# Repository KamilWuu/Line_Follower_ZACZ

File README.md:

# Line_Follower_ZACZ
LineFollower robot created with my friend Oliwier W. Robot is made as a project for a mobile robots course in the sixth semester of the automation and robotics program at the Wrocaw University of Science and Technology.

test213

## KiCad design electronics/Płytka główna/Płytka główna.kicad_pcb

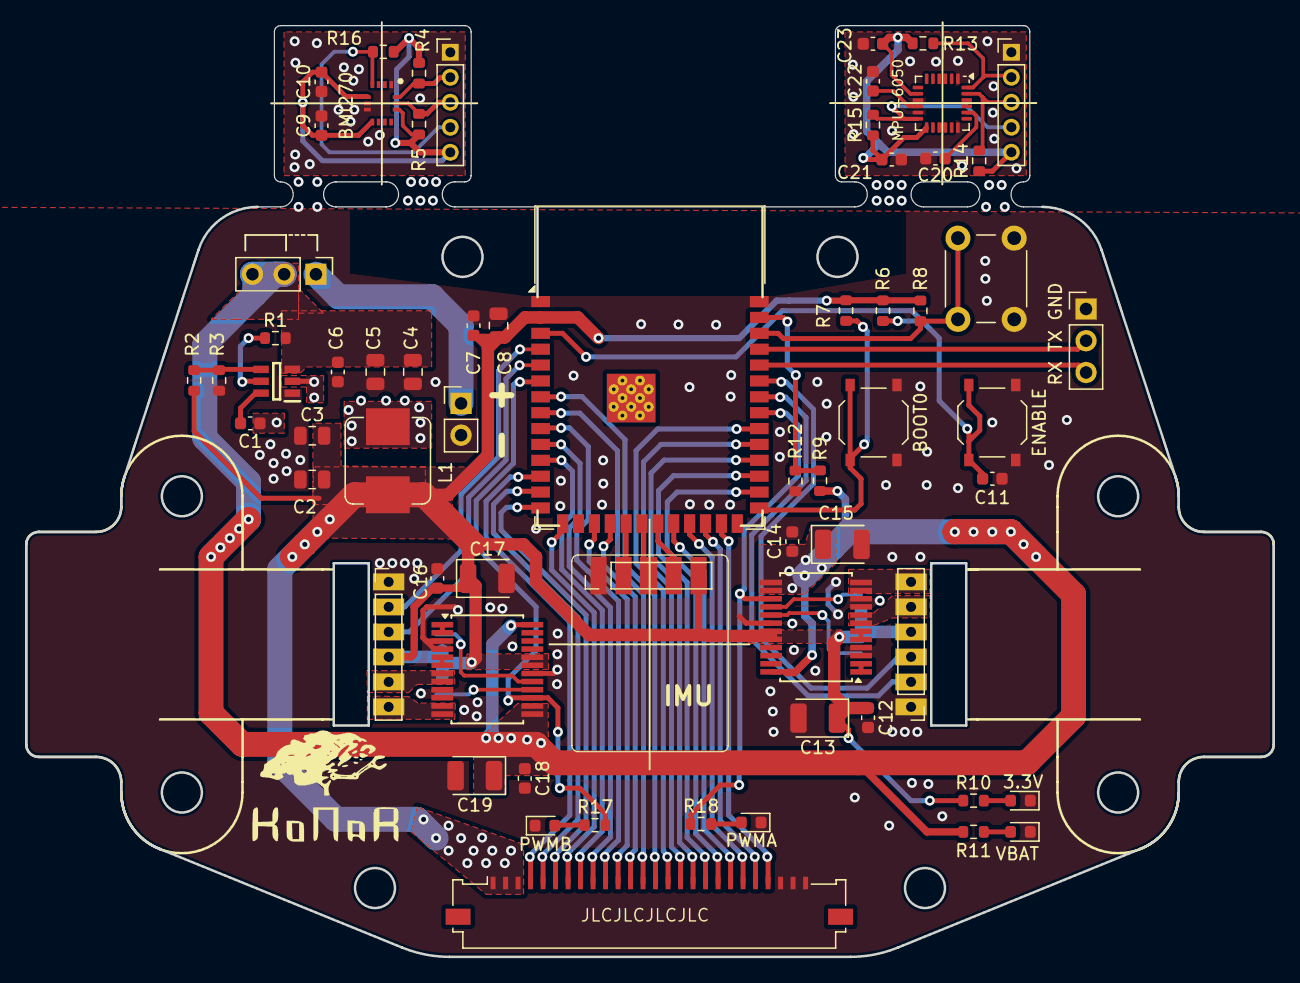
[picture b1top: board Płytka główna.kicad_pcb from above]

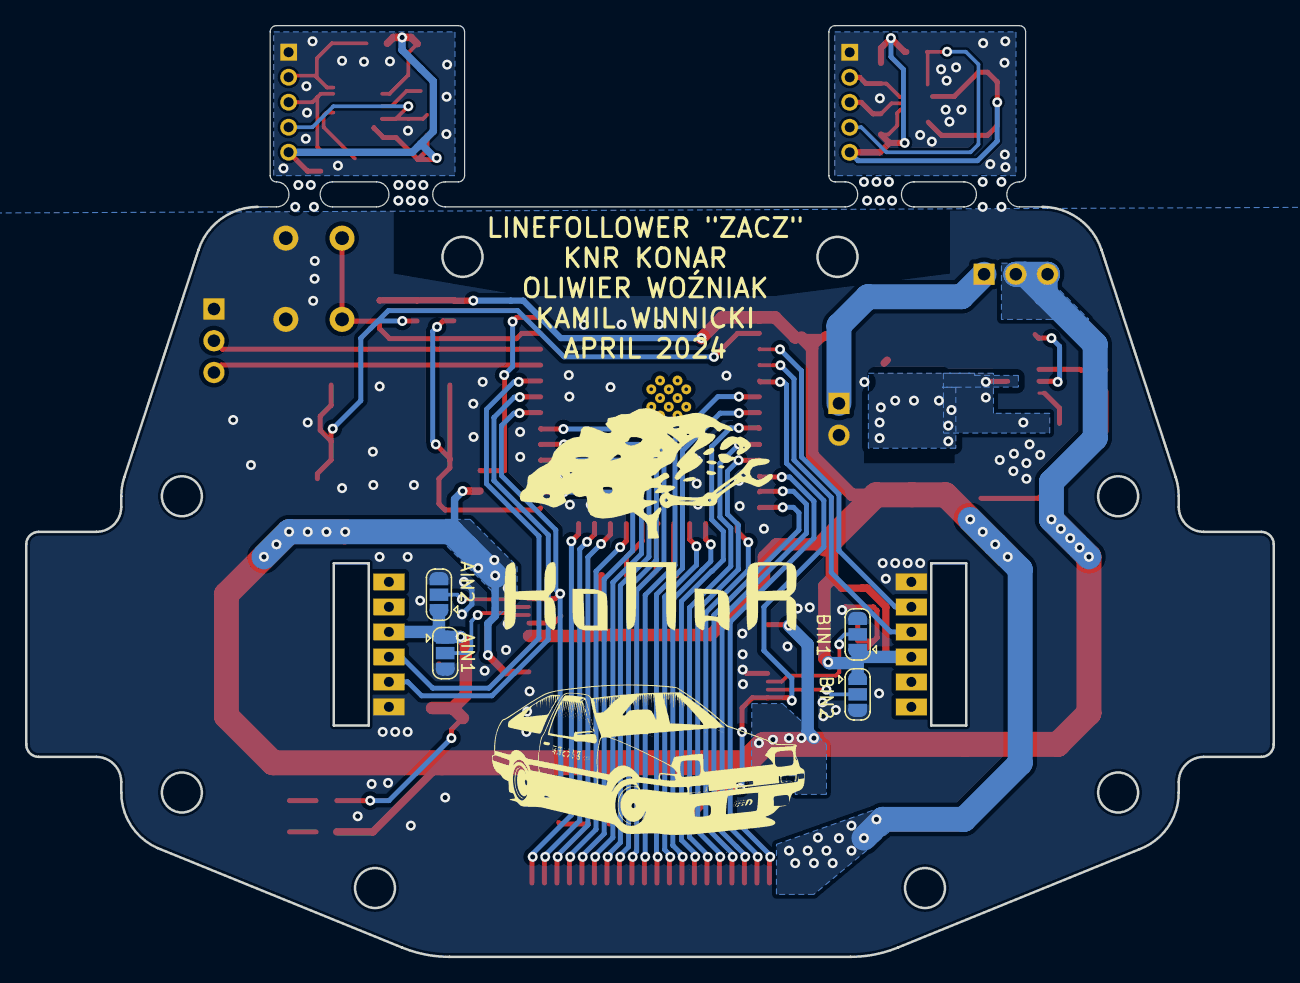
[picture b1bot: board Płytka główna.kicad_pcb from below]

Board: 2 copper layers, 99.8 x 74.5 mm, 68 parts (4 on the bottom side), 71 nets.

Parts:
3.3V: LED; LED_0603_1608Metric
AIN1, AIN2: SolderJumper_3_Open; SolderJumper-3_P1.3mm_Open_RoundedPad1.0x1.5mm
BIN1, BIN2: SolderJumper_3_Open; SolderJumper-3_P1.3mm_Open_RoundedPad1.0x1.5mm
BOOT0: SW_Push_Dual_x2; SW_Push_1P1T_XKB_TS-1187A
C1, C6, C7, C9, C10, C11, C12, C14, C16, C18, C21, C22: 0.1uF; C_0603_1608Metric
C2, C3, C8: 22uF; C_0805_2012Metric
C4, C5: 10uF; C_0805_2012Metric
C13, C17: >10uF/3.3V; CP_EIA-3528-21_Kemet-B
C15, C19: >10uF/8.4V; CP_EIA-3528-21_Kemet-B
C20: 2.2nF; C_0603_1608Metric
C23: 10nF; C_0603_1608Metric
ENABLE: SW_Push_Dual_x2; SW_Push_1P1T_XKB_TS-1187A
IC1: TPS563201DDCR; SOT95P280X110-6N
IC2: BMI270; QFN50P300X250X87-14N
J2: Conn_01x26_Socket; Molex_200528-0260_1x26-1MP_P1.00mm_Horizontal
J3, J4: Conn_01x06_Socket; PinHeader_1x06_P2.00mm_Vertical
J5: battery_connector; PinHeader_1x02_P2.54mm_Vertical
J6: Conn_01x03_Pin; PinHeader_1x03_P2.54mm_Vertical
J7: batt_switch; PinHeader_1x03_P2.54mm_Vertical
J8, J9, J10: Conn_01x05_Pin; PinHeader_1x05_P2.00mm_Vertical
L1: 2.2uH; L_Bourns_SRP7028A_7.3x6.6mm
MPU-6050: MPU-6050; InvenSense_QFN-24_4x4mm_P0.5mm
PWMA: LED; LED_0603_1608Metric
PWMB: LED; LED_0603_1608Metric
R1, R3: 10kR; R_0603_1608Metric
R2: 33.2kR; R_0603_1608Metric
R4, R5, R6, R7, R8, R13, R14, R15, R16: 10K; R_0603_1608Metric
R9, R12: ?; R_0603_1608Metric
R10: 220; R_0603_1608Metric
R11, R17, R18: 2K; R_0603_1608Metric
SW4: SW_Push_Dual_x2; SW_PUSH_6mm_H7.3mm
U1: ESP32-S3-WROOM-1-N8R8; ESP32-S3-WROOM-1
U2, U3: TB6612FNG; SSOP-24_5.3x8.2mm_P0.65mm
VBAT: LED; LED_0603_1608Metric

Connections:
+3.3V: AIN1.1 (A), AIN2.1 (A), BIN1.1 (A), BIN2.1 (A), C2.2, C3.2, C7.2, C8.2, C12.1, C13.1, C16.1, C17.1, J2.1, J2.2, J2.3, J3.4, J4.4, J9.5, L1.1, R2.2, R6.1, R7.1, R8.1, R10.1, U1.2 (3V3), U2.19 (STBY), U2.20 (VCC), U3.19 (STBY), U3.20 (VCC)
+3.3V_BMI: C9.1, C10.2, IC2.5 (VDDIO), IC2.8 (VDD), IC2.12 (CSB), J10.5, R4.1, R5.1, R16.1
+3.3V_MPU: C21.2, C23.2, J8.5, MPU-6050.8 (VLOGIC), MPU-6050.13 (VDD), R13.1, R14.1, R15.1
+BATT: C4.1, C5.1, C6.1, C14.1, C15.1, C18.1, C19.1, IC1.3 (VIN), J7.2, J7.3, R1.2, R9.1, R11.1, U2.13 (VM2), U2.14 (VM3), U2.24 (VM1), U3.13 (VM2), U3.14 (VM3), U3.24 (VM1)
AIN1: AIN1.2 (C), U2.17 (BIN1)
AIN2: AIN2.2 (C), U2.16 (BIN2)
AO1: J3.6, U2.11 (BO1), U2.12 (BO1)
AO2: J3.5, U2.7 (BO2), U2.8 (BO2)
BIN1: BIN1.2 (C), U3.17 (BIN1)
BIN2: BIN2.2 (C), U3.16 (BIN2)
BO1: J4.6, U3.11 (BO1), U3.12 (BO1)
BO2: J4.5, U3.7 (BO2), U3.8 (BO2)
BUTTON: R8.2, SW4.2 (D), U1.38 (IO2)
EN: C11.2, ENABLE.2 (D), R6.2, U1.3 (EN)
ENC_A1: J3.3, U1.35 (IO42)
ENC_A2: J3.2, U1.34 (IO41)
ENC_B1: J4.3, U1.5 (IO5)
ENC_B2: J4.2, U1.4 (IO4)
GND: 3.3V.1 (K), AIN1.3 (B), AIN2.3 (B), BIN1.3 (B), BIN2.3 (B), BOOT0.1 (C), C2.1, C3.1, C4.2, C5.2, C6.2, C7.1, C8.1, C11.1, C12.2, C13.2, C14.2, C15.2, C16.2, C17.2, C18.2, C19.2, ENABLE.1 (C), IC1.1 (GND), J2.24, J2.25, J2.26, J3.1, J4.1, J5.2, J6.1, J9.1, PWMA.1 (K), PWMB.1 (K), R3.1, R12.2, SW4.1 (C), U1.1 (GND), U1.40 (GND), U2.3 (PGND1), U2.4 (PGND1), U2.9 (PGND2), U2.10 (PGND2), U2.18 (GND), U3.3 (PGND1), U3.4 (PGND1), U3.9 (PGND2), U3.10 (PGND2), U3.18 (GND), VBAT.1 (K)
GND_BMI: C9.2, C10.1, IC2.1 (SDO), IC2.6 (GNDIO), IC2.7 (GND), J10.1
GND_MPU: C20.1, C21.1, C22.2, C23.1, J8.1, MPU-6050.1 (CLKIN), MPU-6050.9 (AD0), MPU-6050.11 (FSYNC), MPU-6050.18 (GND)
IMU_INT: J9.4, U1.21 (IO13)
INT_BMI: IC2.4 (INT1), J10.4, R16.2
INT_MPU: J8.4, MPU-6050.12 (INT), R15.2
IO0: BOOT0.2 (D), R7.2, U1.27 (IO0)
IR_SIG_01: J2.4, U1.12 (IO8)
IR_SIG_02: J2.5, U1.13 (IO19)
IR_SIG_03: J2.6, U1.14 (IO20)
IR_SIG_04: J2.7, U1.15 (IO3)
IR_SIG_05: J2.8, U1.11 (IO18)
IR_SIG_06: J2.9, U1.10 (IO17)
IR_SIG_07: J2.10, U1.9 (IO16)
IR_SIG_08: J2.11, U1.17 (IO9)
IR_SIG_09: J2.12, U1.18 (IO10)
IR_SIG_10: J2.13, U1.8 (IO15)
IR_SIG_11: J2.14, U1.7 (IO7)
IR_SIG_12: J2.15, U1.32 (IO39)
IR_SIG_13: J2.16, U1.31 (IO38)
IR_SIG_14: J2.17, U1.30 (IO37)
IR_SIG_15: J2.18, U1.29 (IO36)
IR_SIG_16: J2.19, U1.28 (IO35)
IR_SIG_17: J2.20, U1.22 (IO14)
IR_SIG_18: J2.21, U1.23 (IO21)
IR_SIG_19: J2.22, U1.24 (IO47)
IR_SIG_20: J2.23, U1.25 (IO48)
unnamed: 3.3V.2 (A), R10.2
unnamed: IC1.5 (EN), R1.1
unnamed: C1.2, IC1.6 (VBST)
unnamed: IC1.4 (VFB), R2.1, R3.2
unnamed: J5.1, J7.1
unnamed: C20.2, MPU-6050.20 (CPOUT)
unnamed: C22.1, MPU-6050.10 (REGOUT)
unnamed: PWMA.2 (A), R18.2
unnamed: PWMB.2 (A), R17.2
unnamed: U2.1 (AO1), U2.2 (AO1)
unnamed: U2.5 (AO2), U2.6 (AO2)
unnamed: U3.1 (AO1), U3.2 (AO1)
unnamed: U3.5 (AO2), U3.6 (AO2)
unnamed: R11.2, VBAT.2 (A)
PWMA: R18.1, U1.33 (IO40), U2.15 (PWMB)
PWMB: R17.1, U1.6 (IO6), U3.15 (PWMB)
RX: J6.3, U1.36 (RXD0)
SCL_I2C: J9.3, U1.20 (IO12)
SCL_I2C_BMI: IC2.13 (SCX), J10.3, R5.2
SCL_I2C_MPU: J8.3, MPU-6050.23 (SCL), R14.2
SDA_I2C: J9.2, U1.19 (IO11)
SDA_I2C_BMI: IC2.14 (SDX), J10.2, R4.2
SDA_I2C_MPU: J8.2, MPU-6050.24 (SDA), R13.2
SW: C1.1, IC1.2 (SW), L1.2
TX: J6.2, U1.37 (TXD0)
V_BAT: R9.2, R12.1, U1.39 (IO1)

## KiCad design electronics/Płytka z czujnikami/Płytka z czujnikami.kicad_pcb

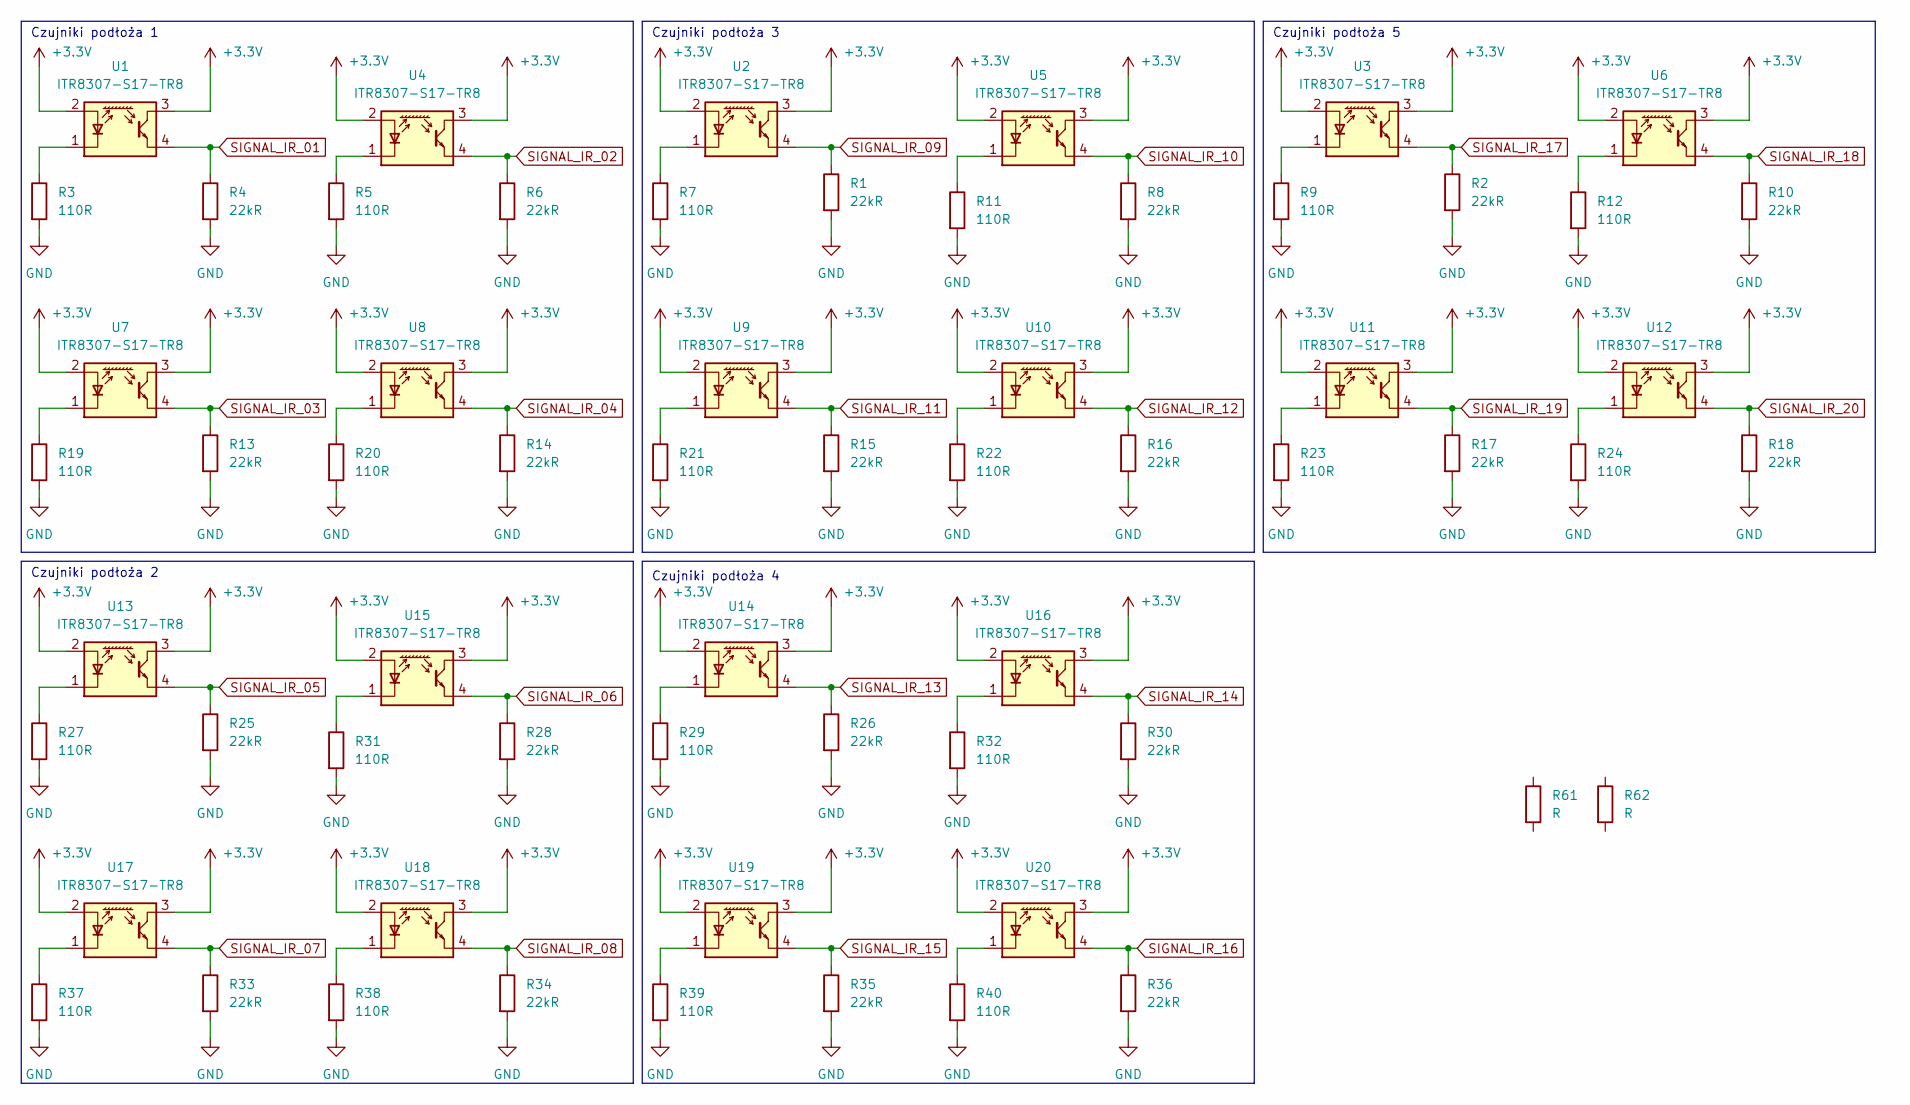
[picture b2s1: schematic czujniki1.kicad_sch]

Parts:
R1, R2, R4, R6, R8, R10, R13, R14, R15, R16, R17, R18, R25, R26, R28, R30, R33, R34, R35, R36: 22kR; R_0402_1005Metric_Pad0.72x0.64mm_HandSolder
R3, R5, R7, R9, R11, R12, R19, R20, R21, R22, R23, R24, R27, R29, R31, R32, R37, R38, R39, R40: 110R; R_0402_1005Metric_Pad0.72x0.64mm_HandSolder
R61, R62: R; R_Axial_DIN0207_L6.3mm_D2.5mm_P10.16mm_Horizontal
U1, U2, U3, U4, U5, U6, U7, U8, U9, U10, U11, U12, U13, U14, U15, U16, U17, U18, U19, U20: ITR8307-S17-TR8; Everlight_ITR1201SR10AR

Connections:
+3.3V: U1.2 (A), U1.3, U2.2 (A), U2.3, U3.2 (A), U3.3, U4.2 (A), U4.3, U5.2 (A), U5.3, U6.2 (A), U6.3, U7.2 (A), U7.3, U8.2 (A), U8.3, U9.2 (A), U9.3, U10.2 (A), U10.3, U11.2 (A), U11.3, U12.2 (A), U12.3, U13.2 (A), U13.3, U14.2 (A), U14.3, U15.2 (A), U15.3, U16.2 (A), U16.3, U17.2 (A), U17.3, U18.2 (A), U18.3, U19.2 (A), U19.3, U20.2 (A), U20.3; also elsewhere on the board
GND: R1.2, R2.2, R3.2, R4.2, R5.2, R6.2, R7.2, R8.2, R9.2, R10.2, R11.2, R12.2, R13.2, R14.2, R15.2, R16.2, R17.2, R18.2, R19.2, R20.2, R21.2, R22.2, R23.2, R24.2, R25.2, R26.2, R27.2, R28.2, R29.2, R30.2, R31.2, R32.2, R33.2, R34.2, R35.2, R36.2, R37.2, R38.2, R39.2, R40.2; also elsewhere on the board
unnamed: R3.1, U1.1 (K)
unnamed: R7.1, U2.1 (K)
unnamed: R9.1, U3.1 (K)
unnamed: R5.1, U4.1 (K)
unnamed: R11.1, U5.1 (K)
unnamed: R12.1, U6.1 (K)
unnamed: R19.1, U7.1 (K)
unnamed: R20.1, U8.1 (K)
unnamed: R21.1, U9.1 (K)
unnamed: R22.1, U10.1 (K)
unnamed: R23.1, U11.1 (K)
unnamed: R24.1, U12.1 (K)
unnamed: R27.1, U13.1 (K)
unnamed: R29.1, U14.1 (K)
unnamed: R31.1, U15.1 (K)
unnamed: R32.1, U16.1 (K)
unnamed: R37.1, U17.1 (K)
unnamed: R38.1, U18.1 (K)
unnamed: R39.1, U19.1 (K)
unnamed: R40.1, U20.1 (K)
SIGNAL_IR_01: R4.1, U1.4; also elsewhere on the board
SIGNAL_IR_02: R6.1, U4.4; also elsewhere on the board
SIGNAL_IR_03: R13.1, U7.4; also elsewhere on the board
SIGNAL_IR_04: R14.1, U8.4; also elsewhere on the board
SIGNAL_IR_05: R25.1, U13.4; also elsewhere on the board
SIGNAL_IR_06: R28.1, U15.4; also elsewhere on the board
SIGNAL_IR_07: R33.1, U17.4; also elsewhere on the board
SIGNAL_IR_08: R34.1, U18.4; also elsewhere on the board
SIGNAL_IR_09: R1.1, U2.4; also elsewhere on the board
SIGNAL_IR_10: R8.1, U5.4; also elsewhere on the board
SIGNAL_IR_11: R15.1, U9.4; also elsewhere on the board
SIGNAL_IR_12: R16.1, U10.4; also elsewhere on the board
SIGNAL_IR_13: R26.1, U14.4; also elsewhere on the board
SIGNAL_IR_14: R30.1, U16.4; also elsewhere on the board
SIGNAL_IR_15: R35.1, U19.4; also elsewhere on the board
SIGNAL_IR_16: R36.1, U20.4; also elsewhere on the board
SIGNAL_IR_17: R2.1, U3.4; also elsewhere on the board
SIGNAL_IR_18: R10.1, U6.4; also elsewhere on the board
SIGNAL_IR_19: R17.1, U11.4; also elsewhere on the board
SIGNAL_IR_20: R18.1, U12.4; also elsewhere on the board

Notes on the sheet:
Czujniki podłoża 2
Czujniki podłoża 4
Czujniki podłoża 5
Czujniki podłoża 1
Czujniki podłoża 3

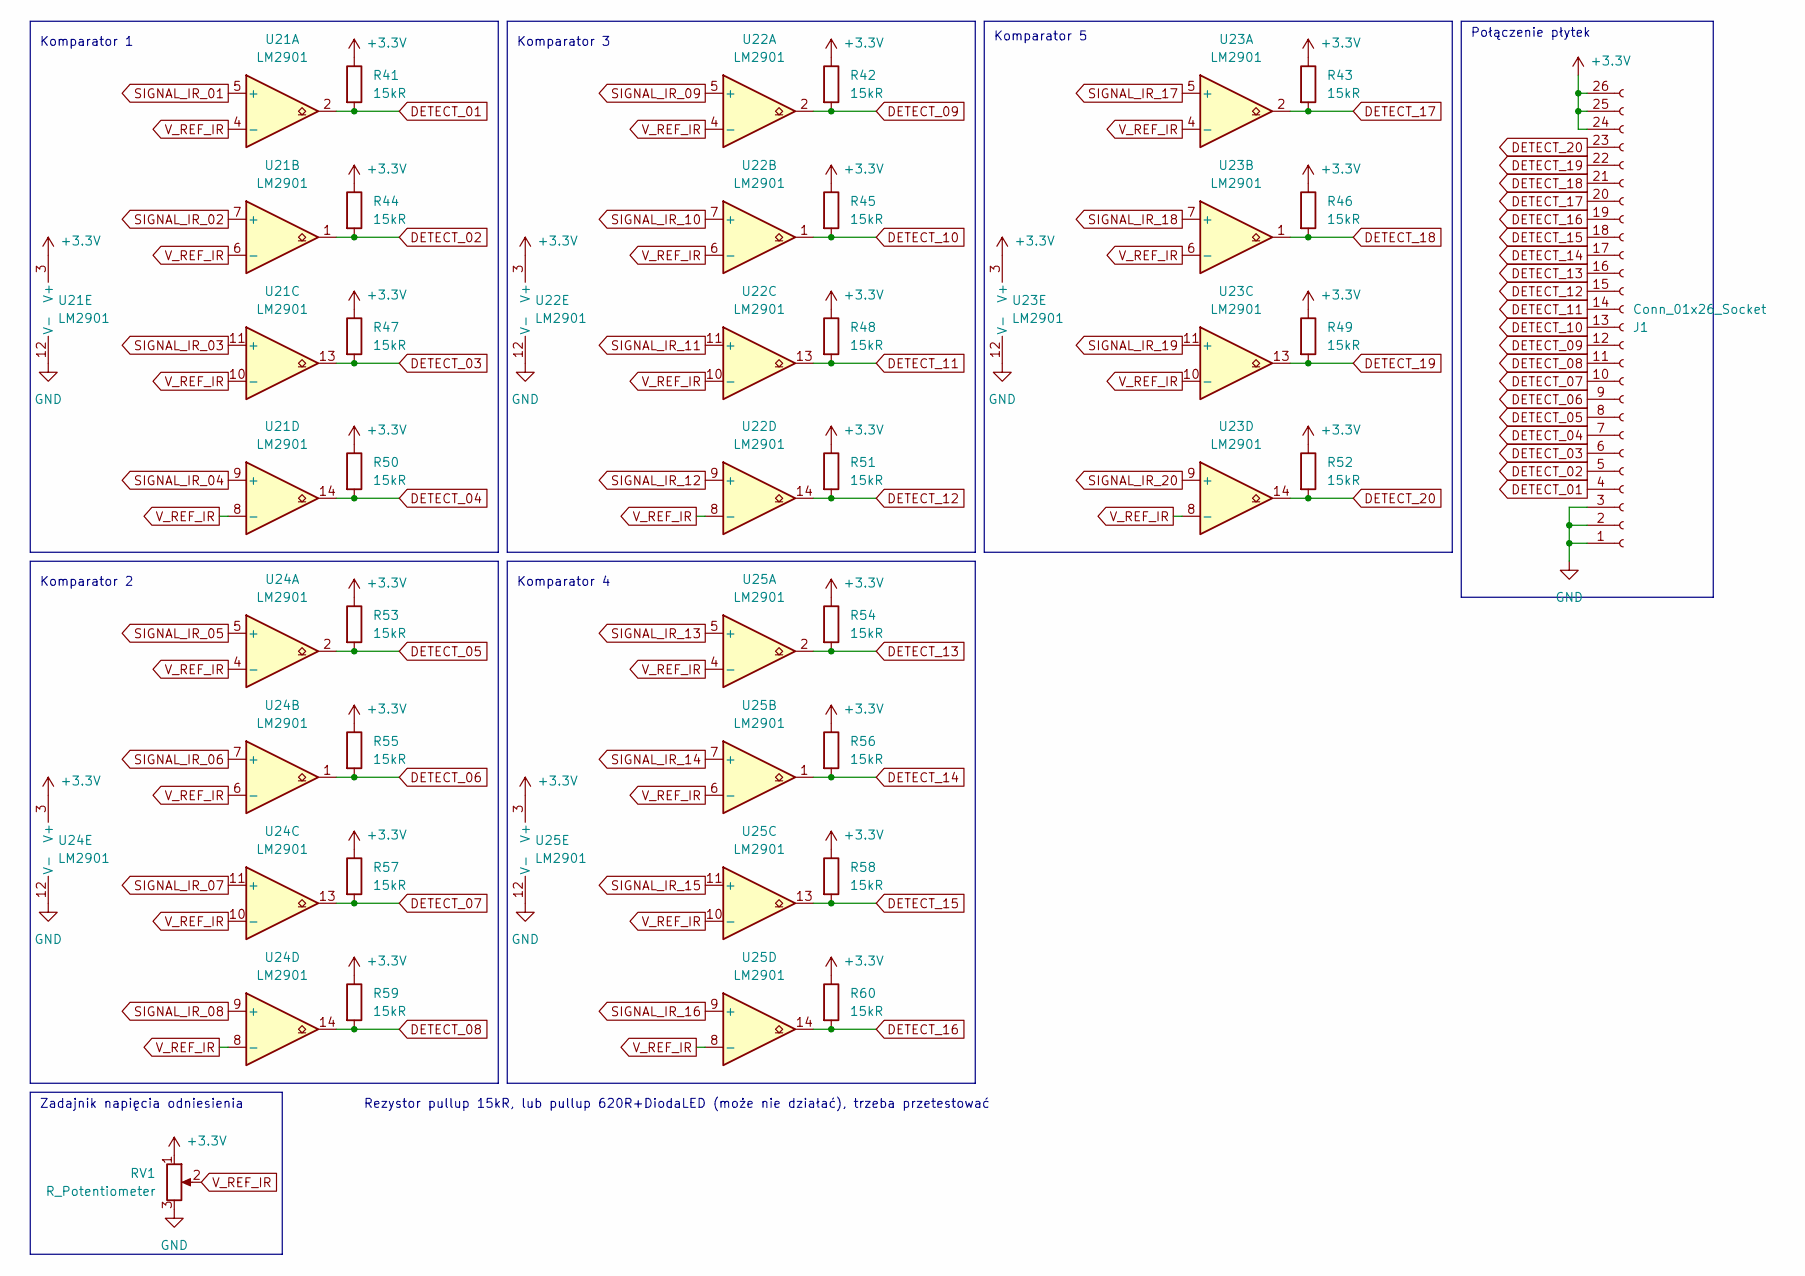
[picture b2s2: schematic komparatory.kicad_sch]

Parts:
J1: Conn_01x26_Socket; Molex_200528-0260_1x26-1MP_P1.00mm_Horizontal
R41, R42, R43, R44, R45, R46, R47, R48, R49, R50, R51, R52, R53, R54, R55, R56, R57, R58, R59, R60: 15kR; R_0402_1005Metric_Pad0.72x0.64mm_HandSolder
RV1: R_Potentiometer; Potentiometer_Vishay_TS53YJ_Vertical
U21, U22, U23, U24, U25: LM2901; SO-14_5.3x10.2mm_P1.27mm

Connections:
+3.3V: J1.24, J1.25, J1.26, R41.1, R42.1, R43.1, R44.1, R45.1, R46.1, R47.1, R48.1, R49.1, R50.1, R51.1, R52.1, R53.1, R54.1, R55.1, R56.1, R57.1, R58.1, R59.1, R60.1, RV1.1, U21.3 (V+), U22.3 (V+), U23.3 (V+), U24.3 (V+), U25.3 (V+); also elsewhere on the board
DETECT_01: J1.4, R41.2, U21.2
DETECT_02: J1.5, R44.2, U21.1
DETECT_03: J1.6, R47.2, U21.13
DETECT_04: J1.7, R50.2, U21.14
DETECT_05: J1.8, R53.2, U24.2
DETECT_06: J1.9, R55.2, U24.1
DETECT_07: J1.10, R57.2, U24.13
DETECT_08: J1.11, R59.2, U24.14
DETECT_09: J1.12, R42.2, U22.2
DETECT_10: J1.13, R45.2, U22.1
DETECT_11: J1.14, R48.2, U22.13
DETECT_12: J1.15, R51.2, U22.14
DETECT_13: J1.16, R54.2, U25.2
DETECT_14: J1.17, R56.2, U25.1
DETECT_15: J1.18, R58.2, U25.13
DETECT_16: J1.19, R60.2, U25.14
DETECT_17: J1.20, R43.2, U23.2
DETECT_18: J1.21, R46.2, U23.1
DETECT_19: J1.22, R49.2, U23.13
DETECT_20: J1.23, R52.2, U23.14
GND: J1.1, J1.2, J1.3, RV1.3, U21.12 (V-), U22.12 (V-), U23.12 (V-), U24.12 (V-), U25.12 (V-); also elsewhere on the board
SIGNAL_IR_01: U21.5 (+); also elsewhere on the board
SIGNAL_IR_02: U21.7 (+); also elsewhere on the board
SIGNAL_IR_03: U21.11 (+); also elsewhere on the board
SIGNAL_IR_04: U21.9 (+); also elsewhere on the board
SIGNAL_IR_05: U24.5 (+); also elsewhere on the board
SIGNAL_IR_06: U24.7 (+); also elsewhere on the board
SIGNAL_IR_07: U24.11 (+); also elsewhere on the board
SIGNAL_IR_08: U24.9 (+); also elsewhere on the board
SIGNAL_IR_09: U22.5 (+); also elsewhere on the board
SIGNAL_IR_10: U22.7 (+); also elsewhere on the board
SIGNAL_IR_11: U22.11 (+); also elsewhere on the board
SIGNAL_IR_12: U22.9 (+); also elsewhere on the board
SIGNAL_IR_13: U25.5 (+); also elsewhere on the board
SIGNAL_IR_14: U25.7 (+); also elsewhere on the board
SIGNAL_IR_15: U25.11 (+); also elsewhere on the board
SIGNAL_IR_16: U25.9 (+); also elsewhere on the board
SIGNAL_IR_17: U23.5 (+); also elsewhere on the board
SIGNAL_IR_18: U23.7 (+); also elsewhere on the board
SIGNAL_IR_19: U23.11 (+); also elsewhere on the board
SIGNAL_IR_20: U23.9 (+); also elsewhere on the board
V_REF_IR: RV1.2, U21.4 (-), U21.6 (-), U21.8 (-), U21.10 (-), U22.4 (-), U22.6 (-), U22.8 (-), U22.10 (-), U23.4 (-), U23.6 (-), U23.8 (-), U23.10 (-), U24.4 (-), U24.6 (-), U24.8 (-), U24.10 (-), U25.4 (-), U25.6 (-), U25.8 (-), U25.10 (-)

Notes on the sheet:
Komparator 1
Połączenie płytek
Komparator 4
Komparator 3
Zadajnik napięcia odniesienia
Komparator 2
Komparator 5
Rezystor pullup 15kR, lub pullup 620R+DiodaLED (może nie działać), trzeba przetestować

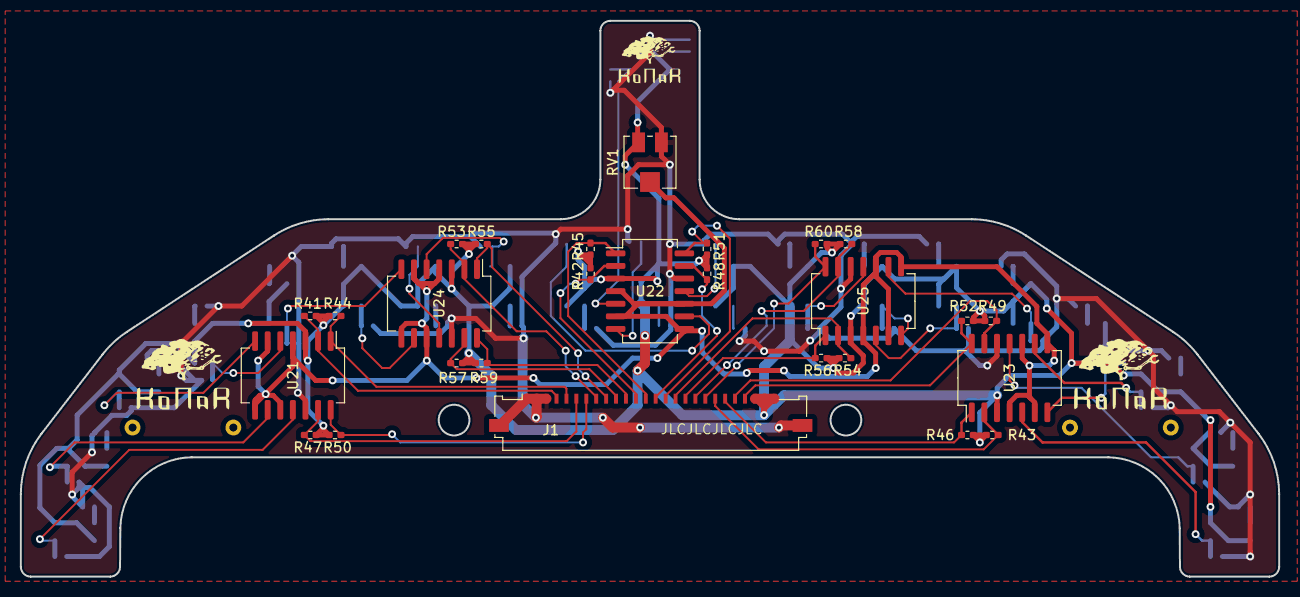
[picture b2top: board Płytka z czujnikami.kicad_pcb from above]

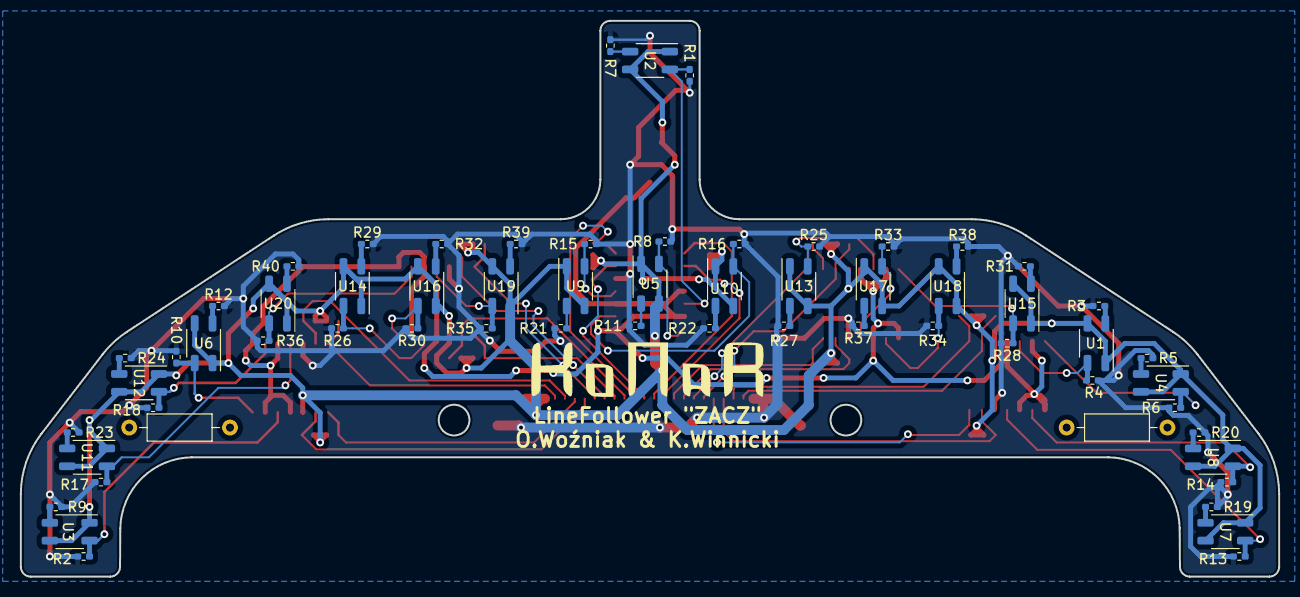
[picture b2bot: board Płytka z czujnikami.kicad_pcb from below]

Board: 2 copper layers, 126.8 x 56.0 mm, 89 parts (62 on the bottom side), 63 nets.

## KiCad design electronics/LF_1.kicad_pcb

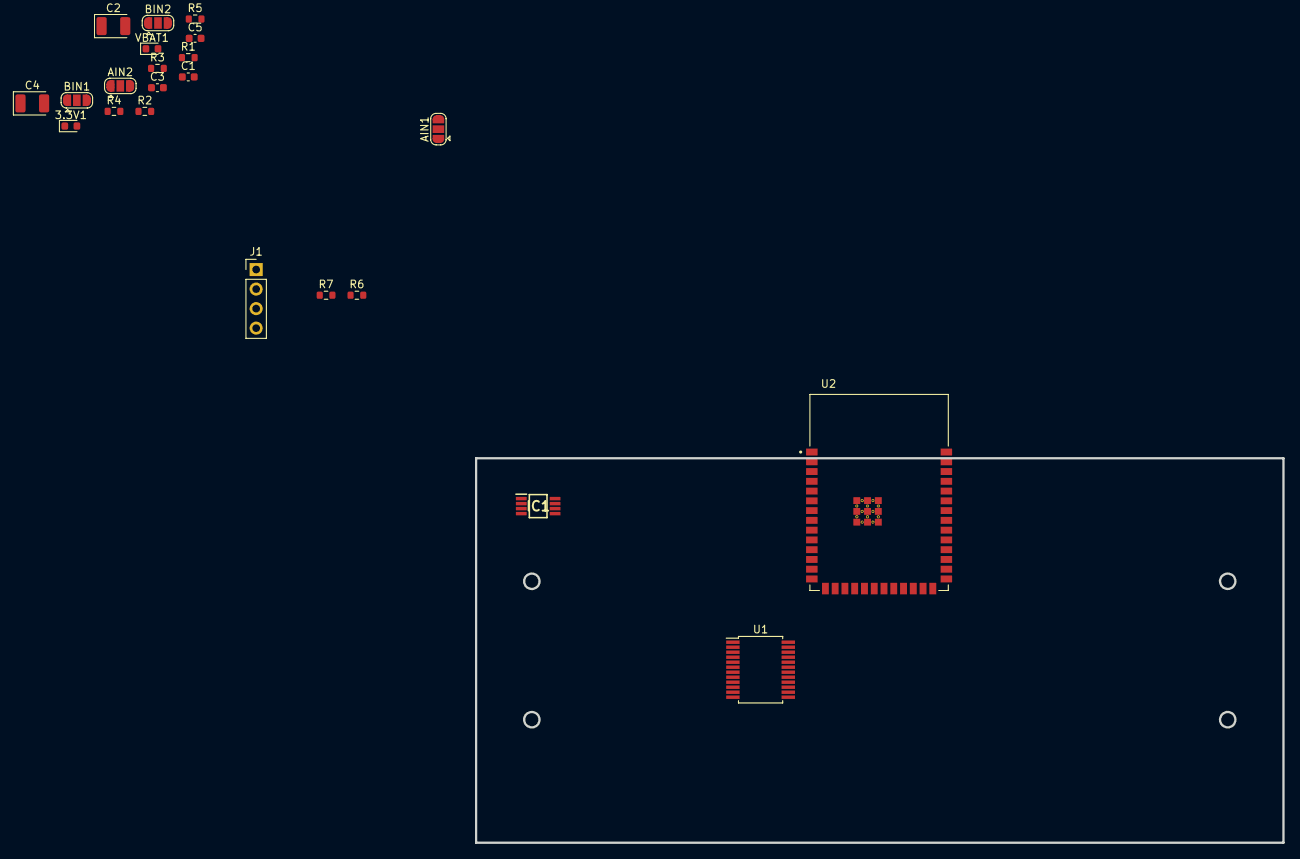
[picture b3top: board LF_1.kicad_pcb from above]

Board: 2 copper layers, 105.0 x 50.0 mm, 22 parts (0 on the bottom side), 20 nets, no tracks yet.

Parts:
3.3V1: LED; LED_0603_1608Metric
AIN1, AIN2: SolderJumper_3_Open; SolderJumper-3_P1.3mm_Open_RoundedPad1.0x1.5mm
BIN1, BIN2: SolderJumper_3_Open; SolderJumper-3_P1.3mm_Open_RoundedPad1.0x1.5mm
C1, C3, C5: 0.1uF; C_0603_1608Metric
C2: >10uF/3.3V; CP_EIA-3528-21_Kemet-B
C4: >10uF/8.4V; CP_EIA-3528-21_Kemet-B
IC1: MCP73844-840I_MS; SOP65P490X110-8N
J1: Conn_01x04_Male; PinHeader_1x04_P2.54mm_Vertical
R1: 220; R_0603_1608Metric
R2: 1K; R_0603_1608Metric
R3, R4, R5, R6, R7: 10K; R_0603_1608Metric
U1: TB6612FNG; SSOP-24_5.3x8.2mm_P0.65mm
U2: ESP32-S3-WROOM-1-N8R8; XCVR_ESP32S3WROOM1N8R8
VBAT1: LED; LED_0603_1608Metric

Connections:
+3.3V: AIN1.1 (A), AIN2.1 (A), BIN1.1 (A), BIN2.1 (A), C1.1, C2.1, J1.4, R1.1, R2.1, R3.1, R4.1, R5.1, U1.19 (STBY), U1.20 (VCC), U2.2 (3V3)
+BATT: C3.1, C4.1, R6.1, U1.13 (VM2), U1.14 (VM3), U1.24 (VM1)
AIN1: AIN1.2 (C), U1.21 (AIN1)
AIN2: AIN2.2 (C), U1.22 (AIN2)
AO1: U1.1 (AO1), U1.2 (AO1)
AO2: U1.5 (AO2), U1.6 (AO2)
BIN1: BIN1.2 (C), U1.17 (BIN1)
BIN2: BIN2.2 (C), U1.16 (BIN2)
BO1: U1.11 (BO1), U1.12 (BO1)
BO2: U1.7 (BO2), U1.8 (BO2)
EN: C5.2, R4.2, U2.3 (EN)
GND: 3.3V1.1 (K), AIN1.3 (B), AIN2.3 (B), BIN1.3 (B), BIN2.3 (B), C1.2, C2.2, C3.2, C4.2, C5.1, J1.1, R7.2, U1.3 (PGND1), U1.4 (PGND1), U1.9 (PGND2), U1.10 (PGND2), U1.18 (GND), U2.1 (GND), U2.40 (GND), U2.41_1 (GND), U2.41_2 (GND), U2.41_3 (GND), U2.41_4 (GND), U2.41_5 (GND), U2.41_6 (GND), U2.41_7 (GND), U2.41_8 (GND), U2.41_9 (GND), VBAT1.1 (K)
IO0: R5.2, U2.27 (IO0)
NIE: U2.16 (IO46), U2.26 (IO45)
unnamed: 3.3V1.2 (A), R1.2
unnamed: R2.2, VBAT1.2 (A)
OK: U2.24 (IO47), U2.25 (IO48), U2.32 (IO39), U2.33 (IO40), U2.34 (IO41), U2.35 (IO42)
RX: J1.3, U2.36 (RXD0)
TX: J1.2, U2.37 (TXD0)
V_BAT: R6.2, R7.1, U2.39 (IO1)

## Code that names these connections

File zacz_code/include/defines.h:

#ifndef DEFINES_H
#define DEFINES_H

#include <Arduino.h>

#define NETWORK     "internet2"
#define PASSWORD    "tak123pl"
#define HOST        "10.42.0.1"
#define PORT        8888

/*INTERFACE*/
#define BATTERY 1
#define BUTTON 2
#define SDA_I2C 11
#define SCL_I2C 12
#define IMU_INT 13



/*LEFT MOTOR*/
#define LEFT_PWM 40
#define LEFT_ENC_2 41
#define LEFT_ENC_1 42

/*RIGHT MOTOR*/

#define RIGHT_PWM 6
#define RIGHT_ENC_2 4
#define RIGHT_ENC_1 5

#endif

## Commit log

2024-03-31 start repository
2024-03-31 ESP and H-Bridge scheme
2024-03-31 added README and some documentation
2024-03-31 some changes in electronics
2024-04-03 Dodano dokumentacje techniczne i opisy do nich
2024-04-03 Podzielono schematy, dodano footprinty
2024-04-03 Dodanie zasilania baterii
2024-04-03 Dodanie zasialnia 3.3V
2024-04-03 Dodano czujniki odbiciowe
2024-04-04 Poprawienie estetyki schematów
2024-04-04 Dodanie IMU
2024-04-09 Podłączenie IMU i poprawa estetyki
2024-04-10 Dodano podział na płytkę przednią i główną
2024-04-10 Zakończono pracę nad układem przedniej płytki
2024-04-10 Niewielkie zmiany w w układzie głównej płytki
2024-04-10 Schematy ideowe ukończone
    Do edycji pozostają jedynie ledy sygnalizacyjne, oraz footprinty od przycisków
2024-04-23 pierwsze prace nad glowna plytka
2024-04-24 drobne zmianmy w mechanice
2024-04-27 Rozpoczęto pracę nad przednią płytką
2024-04-28 test
2024-04-28 test2
2024-04-28 rozpoczeto prace nad plytka glowna
2024-04-29 layout plytki glownej
2024-04-29 Poprawa wymiarów płytki przedniej, oraz wstępne uporządkowanie ułożenia elementów
2024-05-01 zmieniono pinout na zlaczu ffc
2024-05-01 dodatkowe plytki do IMU
2024-05-01 ukonczono glowna plytke
2024-05-02 Ukończono płytkę z czujnikami
2024-05-03 Odwrócono zasilanie w płytce z czujnikami
2024-05-04 ostatnie poprawki
2024-05-04 plytki gotowe do produkcji
2024-05-04 drobne poprawki 2
2024-05-05 plytka glowna gotowa do produkcji
2024-05-05 ostatnia poprawa plytki przed profukcja
2024-05-05 ostatnia poprawa plytki przed profukcja 2
2024-05-24 added code
2024-05-25 wifi dzialagit add .git add .!
2024-05-25 added defines and IR sensors class
2024-05-25 added pid weights for IR sensors
2024-05-26 Dodano obsługę enkoderów i poprawiono ułożenie czujników podłoża
2024-05-26 Poprawione wypisywanie sensorów, dokonano dodatkowych testów.
2024-05-27 usunieto pozostalosci po BT
2024-05-27 Zmieniono obsługę pomiaru prędkości z enkoderów na stałe odcinki czasowe (przerwania + zliczanie impulsów)
2024-05-27 Dodano komentarze do enkodera
2024-05-28 konfiguracja liczenia predkosci pseudo P oraz wiele innych rzeczy
2024-05-29 zmiana wpisywania IP
2024-05-29 zmiana wpisywania IP2
2024-06-05 Napisano poprawny PID, to znaczy działa tylko PD, ale nie sparwdzałem
2024-06-06 W miarę poprawnie diałający PID, trzeba wykonać więcej testów i sprawdzić optymalne nastawy
2024-06-06 Dodano pliki do sprawka
2024-06-08 dodano wykresy do aplikacji Qt
2024-06-08 dodano wstepny obrot na kompasie
2024-06-12 poprawiono wczytywanie pida
2024-06-13 dodano obsluge zmiany jezyka w aplikacji
2024-06-14 dodano strzalki i naprawiono obrot oraz poprawki wizualne
2024-06-14 uratowano kod z opresji
2024-06-14 uporzadkowanie plikow h
2024-06-14 wygenerowano dokumentacje w doxygenie
2024-06-14 poprawki w wykresie, przyciski wciskalne, poprawki w tlumaczeniach
2024-06-15 poprawki
2024-06-16 robot jezdzi!
2024-06-16 dodano obsluge MPU6050 do pomiaru kata w osi Z
2024-06-16 mpu jakos tam dziala
2024-06-16 poprawki poprawki
2024-06-18 dodano zmiane jezyka w plots
2024-06-18 poprawki w dokmumentacji
2024-06-18 utworzono nowa dokumentacje
2024-06-18 poprawki na wykresach
2024-06-22 ostatnie poprawki w dokumentacji
2024-06-22 dodano dokumentacje III etapu
2024-06-23 dodano dokumentacje z aplikacji
